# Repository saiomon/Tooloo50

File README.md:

# Tooloo50
Töölöö50 is 40% tadpole mount keyboard with arrow cluster/40%TKL/numpad.

## Layout
Supports iso/ansi enter, split right shift, wk/wkl, a few bottom row options and 4x3 grid on the right hand side extension.

## Case
3DP case files support some of the possible combinations.

### Hardware list
| Item     | Amount |
| ---      | ---       |
| Tadpole | 8       |
| M2.5 10mm     | 2       |
| M2.5 16mm   (CS)  | 2       |
| M2.5 6mm  (CS)   | 2       |
| M2.5 Heat insert, OD 3.5mm     | 6       |

*Countersunk (CS)

## PCB
PCB supports mx switches, and additionally 4-key hall sensors on wasd for HE option. STM32F072 processor, ESD protection, fuse, smd USB. Possibility for external flash and crystal. KiCad files and production files are included.

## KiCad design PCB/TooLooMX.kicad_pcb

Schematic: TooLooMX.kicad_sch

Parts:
BOOT1: Jumper_2_Open; SolderJumper-2_P1.3mm_Open_Pad1.0x1.5mm
BZ1: Buzzer; MagneticBuzzer_PUI_AT-0927-TT-6-R; not fitted
C1, C4: 100n; C_0402_1005Metric; Manufacturer Part Number CC0402KRX7R8BB104
C2, C3: 1u; C_0805_2012Metric; Manufacturer Part Number CC0805KKX7R8BB105
C5, C11, C13, C15, C16, C17, C18, C19, C20, C21, C22, C23: 100n; C_0402_1005Metric
C6, C7: 16p; C_0402_1005Metric; not fitted
C8: 1u; C_0402_1005Metric
C9: 10n; C_0402_1005Metric
C10: 10u; CP_EIA-3216-10_Kemet-I_Pad1.58x1.35mm_HandSolder; Manufacturer Part Number TAJA106K016RNJ
C12: 4.7u; C_0402_1005Metric; not fitted
C14: 100n; C_0402_1005Metric; Manufacturer Part Number CL05B104KB54PNC
D1, D2, D3, D4, D5, D6, D7, D8, D9, D10, D11, D12, D13, D14, D15, D16, D17, D18, D19, D20, D21, D22, D23, D24, D25, D26, D27, D28, D29, D30, D31, D32, D33, D34, D35, D36, D37, D38, D39, D40, D41, D42, D43, D44, D45, D46, D47, D48, D49, D50, D51, D52, D53, D54, D55, D56, D57, D58, D59, D60, D61: 1N4148W; D_SOD-123; Manufacturer Part Number 1N4148W
D62: RB060M-60TR SS34; D_SMA; Manufacturer Part Number RB060M-60TR SS34
D63: D_Schottky; D_SOD-123F
F1, F2, F3: mSMD110-16V; Fuse_1812_4532Metric; Manufacturer Part Number mSMD110-16V
FB1: CBW201209U121T; L_0805_2012Metric; Manufacturer Part Number CBW201209U121T
HALL1, HALL2, HALL3, HALL4: SLSS49E-3; SOT-23
J1: TYPE-C-31-M12; USB_C_Receptacle_Hroparts_TYPE-C-31-M-12; Manufacturer Part Number TYPE-C-31-M-12
M1: Motor_DC; Buzzer_15x7.5RM7.6; not fitted
NRST1: Jumper_2_Open; SolderJumper-2_P1.3mm_Open_Pad1.0x1.5mm
Q1: 2N7002K; SOT-23
Q2: TIP120; TO-220-3_Vertical; not fitted
R1, R2: 4.7k; R_0402_1005Metric
R3, R4: 100k; R_0805_2012Metric; Manufacturer Part Number RC0805FR-07100KL
R5: 1.5k; R_0402_1005Metric
R6: 51k; R_0402_1005Metric
R7, R8: 5.1k; R_0805_2012Metric; Manufacturer Part Number RC0805FR-075K1L
R9: 10k; R_0402_1005Metric; Manufacturer Part Number 0402WGF1002TCE
R10, R11, R12, R13: 10k; R_0402_1005Metric
R14, R15: 220; R_0805_2012Metric
S1: MX_stab; STAB_MX_P_10u
S2, S4: MX_stab; STAB_MX_P_3u
S3: MX_stab; STAB_MX_P_2.25u
S5: MX_stab; STAB_MX_2u
S6: MX_stab; STAB_MX_P_2.75u
S7: MX_stab; STAB_MX_2.75u
S8: MX_stab; STAB_MX_2.25u
S9: MX_stab; STAB_MX_P_ISO-ROT
SW1, SW2, SW3, SW4, SW5, SW6, SW7, SW8, SW9, SW10, SW11, SW12, SW13, SW14, SW15, SW16, SW18, SW20, SW21, SW22, SW23, SW24, SW25, SW26, SW27, SW28, SW29, SW30, SW31, SW32, SW33, SW34, SW35, SW37, SW38, SW39, SW40, SW41, SW42, SW43, SW44, SW45, SW46, SW47, SW49, SW50, SW51, SW56, SW57, SW58, SW62, SW63, SW64, SW67, SW68, SW69: CPG151101S11; SW_MX_1u; Manufacturer Part Number CPG151101S11
SW17, SW48, SW65, SW66, SW70, SW71: CPG151101S11; SW_MX_1.5u; Manufacturer Part Number CPG151101S11
SW19, SW52, SW53, SW54, SW55, SW59, SW60, SW61: CPG151101S11; SW_MX_1.25u; Manufacturer Part Number CPG151101S11
SW36: CPG151101S11; SW_MX_1.75u; Manufacturer Part Number CPG151101S11
U1: MCP1700T-3302E/TT; SOT-23; Manufacturer Part Number MCP1700T-3302E/TT
U2: STM32F401-LQFP64; LQFP-64_10x10mm_P0.5mm
U3: SRV05-4-P-T7; SOT-23-6-routable; Manufacturer Part Number USBLC6-2SC6
U4: BL24C256A-SFRC; TSSOP-8_4.4x3mm_P0.65mm; Manufacturer Part Number BL24C256A-SFRC; not fitted
X1: ARM JTAG; PinHeader_2x5_P2.54mm_Vertical_Staggered
X2: LED; PinHeader_1x2_P2.54mm_Vertical
Y1: 7325-0800A2010-00; Crystal_SMD_3225-4Pin_3.2x2.5mm; Manufacturer Part Number 7325-0800A2010-00; not fitted

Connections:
3V3: BOOT1.1 (A), C1.2, C3.1, C4.1, C5.2, C8.1, C9.1, C10.1, C11.2, C13.2, C15.2, C17.2, C19.2, C21.2, C23.2, D62.2 (A), HALL1.1 (VDD), HALL2.1 (VDD), HALL3.1 (VDD), HALL4.1 (VDD), R1.1, R2.1, R4.1, R5.1, R6.1, U1.2 (VO), U2.1 (VBAT), U2.13 (VDDA/VREF+), U2.19 (VDD), U2.32 (VDD), U2.48 (VDD), U2.64 (VDD), U4.8 (VCC), X1.7, X1.8
5V: C2.1, D62.1 (K), D63.1 (K), F1.2, M1.1 (+), R3.1, U1.3 (VI)
AI0: C16.1, R10.1, U2.24 (PC4)
AI1: C18.1, R11.1, U2.25 (PC5)
AI2: C20.1, R12.1, U2.26 (PB0/TIM3_CH3)
AI3: C22.1, R13.1, U2.27 (PB1/TIM3_CH4)
BOOT0: BOOT1.2 (B), R9.2, U2.60 (BOOT0), X1.5
BUZ: R15.1, U2.41 (USART1_CK/TIM1_CH1/PA8)
C0: SW1.1, SW2.1, SW19.1, SW36.1, U2.23 (PA7/SPI1_MOSI/TIM3_CH2)
C1: SW3.1, SW20.1, SW37.1, SW53.1, SW65.1, U2.22 (PA6/TIM3_CH1/SPI1_MISO)
C2: SW4.1, SW21.1, SW38.1, SW54.1, U2.21 (PA5/TIM2_CH1/SPI1_SCK)
C3: SW5.1, SW22.1, SW39.1, SW55.1, SW66.1, U2.20 (PA4/USART2_CK)
C4: SW6.1, SW23.1, SW40.1, SW56.1, SW67.1, U2.17 (PA3/TIM2_CH4/USART2_RX)
C5: SW7.1, SW24.1, SW41.1, U2.2 (PC13)
C6: SW8.1, SW25.1, SW42.1, SW57.1, SW68.1, U2.3 (PC14/OSC32_IN)
C7: SW9.1, SW26.1, SW43.1, U2.4 (PC15/OSC32_OUT)
C8: SW10.1, SW27.1, SW44.1, SW58.1, SW69.1, U2.8 (PC0)
C9: SW11.1, SW28.1, SW45.1, U2.16 (PA2/TIM2_CH3/USART2_TX)
C10: SW12.1, SW29.1, SW46.1, SW59.1, SW70.1, U2.15 (PA1/TIM2_CH2/USART2_RTS)
C11: SW13.1, SW30.1, SW47.1, SW52.1, SW60.1, U2.14 (PA0/TIM2_CH1/USART2_CTS)
C12: SW17.1, SW18.1, SW31.1, SW35.1, SW48.1, SW61.1, SW71.1, U2.39 (USART6_CK/TIM3_CH3/PC8)
C13: SW14.1, SW32.1, SW49.1, SW62.1, U2.57 (SPI1_MOSI/SPI3_MOSI/TIM3_CH2/PB5)
C14: SW15.1, SW33.1, SW50.1, SW63.1, U2.56 (NJTRST/SPI1_MISO/SPI3_MISO/I2C3_SDA/TIM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)
C15: SW16.2, SW34.2, SW51.2, SW64.2, U2.55 (JTDO-SWO/SPI1_SCK/SPI3_SCK/I2C2_SDA/TIM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)
D+: J1.A6 (D+), J1.B6 (D+), R5.2, U2.45 (OTG_FS_DP/USART6_RX/PA12), U3.1 (IO1)
D-: J1.A7 (D-), J1.B7 (D-), U2.44 (OTG_FS_DM/TIM1_CH4/USART6_TX/PA11), U3.3 (IO2)
GND: BZ1.2 (-), C1.1, C2.2, C3.2, C4.2, C5.1, C6.2, C7.2, C8.2, C9.2, C10.2, C11.1, C12.1, C13.1, C14.2, C15.1, C16.2, C17.1, C18.2, C19.1, C20.2, C21.1, C22.2, C23.1, FB1.1, HALL1.2 (GND), HALL2.2 (GND), HALL3.2 (GND), HALL4.2 (GND), J1.A1 (GND), J1.B1 (GND), NRST1.1 (A), Q1.2 (S), Q2.3 (E), R3.2, R4.2, R7.1, R8.1, R9.1, U1.1 (GND), U2.12 (VSSA/VREF-), U2.18 (VSS), U2.31 (VSS), U2.47 (VSS), U2.63 (VSS), U3.2 (VN), U4.1 (A0), U4.2 (A1), U4.3 (A2), U4.4 (GND), U4.7 (WP), X1.3, X1.4, X1.10, X2.2, Y1.2, Y1.4
GNDPWR: FB1.2, J1.S (SHIELD)
LED_PWM: U2.9 (PC1), X2.1
NRST: C14.1, NRST1.2 (B), U2.7 (NRST), X1.9
unnamed: BZ1.1 (+), R15.2
unnamed: D1.2 (A), SW1.2
unnamed: D2.2 (A), SW2.2
unnamed: D3.2 (A), SW3.2
unnamed: D4.2 (A), SW4.2
unnamed: D5.2 (A), SW5.2
unnamed: D6.2 (A), SW6.2
unnamed: D7.2 (A), SW7.2
unnamed: D8.2 (A), SW8.2
unnamed: D9.2 (A), SW9.2
unnamed: D10.2 (A), SW10.2
unnamed: D11.2 (A), SW11.2
unnamed: D12.2 (A), SW12.2
unnamed: D13.2 (A), SW13.2
unnamed: D14.2 (A), SW14.2
unnamed: D15.2 (A), SW15.2
unnamed: D16.2 (A), SW16.1
unnamed: D17.2 (A), SW17.2, SW18.2
unnamed: D18.2 (A), SW19.2
unnamed: D19.2 (A), SW20.2
unnamed: D20.2 (A), SW21.2
unnamed: D21.2 (A), SW22.2
unnamed: D22.2 (A), SW23.2
unnamed: D23.2 (A), SW24.2
unnamed: D24.2 (A), SW25.2
unnamed: D25.2 (A), SW26.2
unnamed: D26.2 (A), SW27.2
unnamed: D27.2 (A), SW28.2
unnamed: D28.2 (A), SW29.2
unnamed: D29.2 (A), SW30.2
unnamed: D30.2 (A), SW31.2, SW35.2
unnamed: D31.2 (A), SW32.2
unnamed: D32.2 (A), SW33.2
unnamed: D33.2 (A), SW34.1
unnamed: D34.2 (A), SW36.2
unnamed: D35.2 (A), SW37.2
unnamed: D36.2 (A), SW38.2
unnamed: D37.2 (A), SW39.2
unnamed: D38.2 (A), SW40.2
unnamed: D39.2 (A), SW41.2
unnamed: D40.2 (A), SW42.2
unnamed: D41.2 (A), SW43.2
unnamed: D42.2 (A), SW44.2
unnamed: D43.2 (A), SW45.2
unnamed: D44.2 (A), SW46.2
unnamed: D45.2 (A), SW47.2, SW52.2
unnamed: D46.2 (A), SW48.2
unnamed: D47.2 (A), SW49.2
unnamed: D48.2 (A), SW50.2
unnamed: D49.2 (A), SW51.1
unnamed: D50.2 (A), SW53.2, SW65.2
unnamed: D51.2 (A), SW54.2
unnamed: D52.2 (A), SW55.2, SW66.2
unnamed: D53.2 (A), SW56.2, SW67.2
unnamed: D54.2 (A), SW57.2, SW68.2
unnamed: D55.2 (A), SW58.2, SW69.2
unnamed: D56.2 (A), SW59.2, SW70.2
unnamed: D57.2 (A), SW60.2
unnamed: D58.2 (A), SW61.2, SW71.2
unnamed: D59.2 (A), SW62.2
unnamed: D60.2 (A), SW63.2
unnamed: D61.2 (A), SW64.1
unnamed: D63.2 (A), M1.2 (-), Q1.3 (D), Q2.2 (C)
unnamed: HALL1.3 (VOUT), R10.2
unnamed: HALL2.3 (VOUT), R11.2
unnamed: HALL3.3 (VOUT), R12.2
unnamed: HALL4.3 (VOUT), R13.2
unnamed: J1.A5 (CC1), R7.2
unnamed: J1.B5 (CC2), R8.2
unnamed: Q1.1 (G), Q2.1 (B), R14.2
unnamed: R6.2, U2.43 (USART1_RX/TIM1_CH3/PA10)
unnamed: C12.2, U2.30 (VCAP1)
PA9: U2.42 (USART1_TX/TIM1_CH2/PA9)
PB2/BOOT1: U2.28 (PB2), X1.6
PB13: U2.34 (SPI2_SCK/I2S2_CK/PB13)
R0: D2.1 (K), D3.1 (K), D4.1 (K), D5.1 (K), D6.1 (K), D7.1 (K), D8.1 (K), D9.1 (K), D10.1 (K), D11.1 (K), D12.1 (K), D13.1 (K), D14.1 (K), D15.1 (K), D16.1 (K), D17.1 (K), U2.51 (SPI3_SCK/I2S3_CK/PC10)
R1: D18.1 (K), D19.1 (K), D20.1 (K), D21.1 (K), D22.1 (K), D23.1 (K), D24.1 (K), D25.1 (K), D26.1 (K), D27.1 (K), D28.1 (K), D29.1 (K), D30.1 (K), D31.1 (K), D32.1 (K), D33.1 (K), U2.52 (SPI3_MISO/PC11)
R2: D34.1 (K), D35.1 (K), D36.1 (K), D37.1 (K), D38.1 (K), D39.1 (K), D40.1 (K), D41.1 (K), D42.1 (K), D43.1 (K), D44.1 (K), D45.1 (K), D46.1 (K), D47.1 (K), D48.1 (K), D49.1 (K), U2.61 (I2C1_SCL/TIM4_CH3/TIM10_CH1/PB8)
R3: D1.1 (K), D50.1 (K), D51.1 (K), D52.1 (K), D53.1 (K), D54.1 (K), D55.1 (K), D56.1 (K), D57.1 (K), D58.1 (K), D59.1 (K), D60.1 (K), D61.1 (K), U2.62 (I2C1_SDA/TIM4_CH4/TIM11_CH1/PB9)
RGB_3V3: U2.36 (SPI2_MOSI/PB15)
SCL: R2.2, U2.58 (I2C1_SCL/USART1_TX/TIM4_CH1/PB6), U4.6 (SCL)
SDA: R1.2, U2.59 (I2C1_SDA/USART1_RX/TIM4_CH2/PB7), U4.5 (SDA)
SOL: R14.1, U2.50 (JTDI/TIM2_CH1/PA14)
SWCLK: U2.49 (JTCK-SWCLK/PA14), X1.2
SWDIO: U2.46 (JTMS-SWDIO/PA13), X1.1
VBUS: F1.1, J1.A4 (VBUS), J1.B4 (VBUS), U3.5 (VP)
XTAL_IN: C7.1, U2.5 (PH0/OSC_IN), Y1.3
XTAL_OUT: C6.1, U2.6 (PH1/OSC_OUT), Y1.1

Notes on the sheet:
Spooky pin (*)
SWITCH MATRIX
EEPROM
3V3
(*) "Spooky pins": on STM32F4x1, pins A9 and B2 cannot be used for switch matrix: - A9 is meant to be used as a VBUS sensing. It has a undocumented internal pulldown resistor; - B2 is used as BOOT1 during bootup, so it needs an external pulldown for successful bootup; - B13 is locked by the SPI dri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

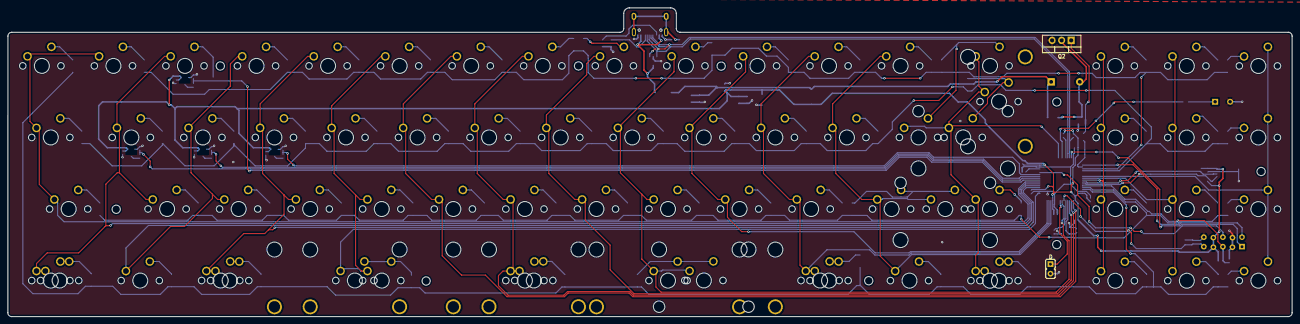
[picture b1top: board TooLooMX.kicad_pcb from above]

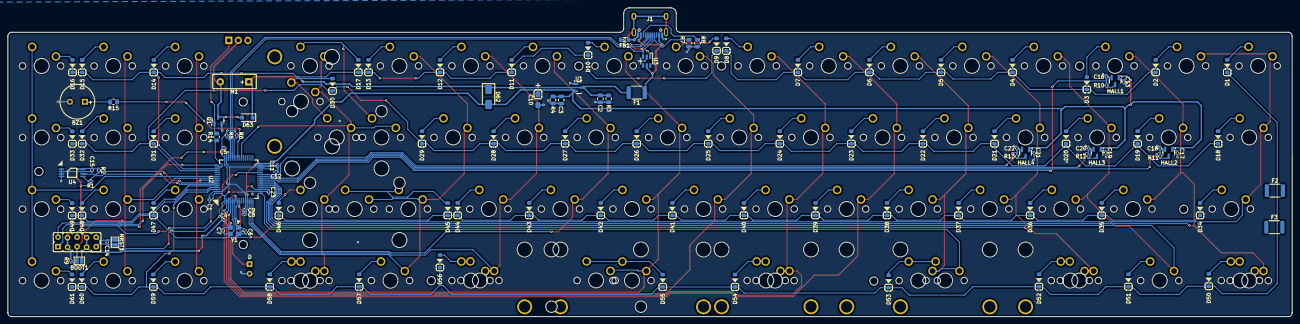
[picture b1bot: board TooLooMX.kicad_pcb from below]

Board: 2 copper layers, 341.9 x 82.2 mm, 203 parts (121 on the bottom side), 115 nets.

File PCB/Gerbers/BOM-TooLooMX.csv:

Comment,Designator,Footprint,LCSC
100k,"R3,R4",R_0805_2012Metric,C149504
10n,C9,C_0402_1005Metric,C15195
100n,"C1,C11,C13,C14,C15,C16,C17,C18,C19,C20,C21,C22,C23,C4,C5",C_0402_1005Metric,C1525
TYPE-C-31-M12,J1,USB_C_Receptacle_Hroparts_TYPE-C-31-M-12,C165948
220,"R14,R15",R_0805_2012Metric,C17557
D_Schottky,D63,D_SOD-123F,C18199087
2N7002K,Q1,SOT-23,C22379475
10k,"R10,R11,R12,R13,R9",R_0402_1005Metric,C25744
51k,R6,R_0402_1005Metric,C25794
1.5k,R5,R_0402_1005Metric,C25867
4.7k,"R1,R2",R_0402_1005Metric,C25900
5.1k,"R7,R8",R_0805_2012Metric,C27834
1u,"C2,C3",C_0805_2012Metric,C28323
SLSS49E-3,"HALL1,HALL2,HALL3,HALL4",SOT-23,C2904393
STM32F401-LQFP64,U2,LQFP-64_10x10mm_P0.5mm,C46046
1u,C8,C_0402_1005Metric,C52923
MCP1700T-3302E/TT,U1,SOT-23,C5446
mSMD110-16V,"F1,F2,F3",Fuse_1812_4532Metric,C69691
10u,C10,CP_EIA-3216-10_Kemet-I_Pad1.58x1.35mm_HandSolder,C7171
1N4148W,"D1,D10,D11,D12,D13,D14,D15,D16,D17,D18,D19,D2,D20,D21,D22,D23,D24,D25,D26,D27,D28,D29,D3,D30,D31,D32,D33,D34,D35,D36,D37,D38,D39,D4,D40,D41,D42,D43,D44,D45,D46,D47,D48,D49,D5,D50,D51,D52,D53,D54,D55,D56,D57,D58,D59,D6,D60,D61,D7,D8,D9",D_SOD-123,C81598
SRV05-4-P-T7,U3,SOT-23-6-routable,C85364
RB060M-60TR SS34,D62,D_SMA,C8678

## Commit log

2024-11-18 Basic info to README.md
2024-11-18 files
2024-11-18 HW list
